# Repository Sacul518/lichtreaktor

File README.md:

# Lichtreaktor

I'm designing a small, round arc-reactor lookalike that produces light in cool patterns. The plan is to press the rotary encoder to switch patterns, and turn it to control the brightness.

The PCB is 90 mm across, with 24 blue LEDs around the edge, a knob in the middle and a XIAO near the top for USB-C access. Six groups of four LEDs will be controlled independently. Tiny reactor, zero fusion involved.

The LEDs look red in KiCad's default 3D model, but the actual parts are blue. The XIAO and rotary encoder don't have 3D models loaded, so their positions look empty here.

## Where it's at

The schematic and PCB layout are done! All 24 LEDs are placed, the traces are routed, and both copper layers have a GND fill. The LEDs, transistors, encoder and XIAO sit on the front; the resistors sit on the back. Getting everything onto a round board took a few attempts, but it fits.

The latest KiCad check (12 October 2026) reports **0 errors, 0 unconnected items and 0 schematic/PCB mismatches**. There are still 24 silkscreen warnings about overlapping print, small text and print near the board edge. Those are accepted for this layout; parts of the print may be clipped during manufacturing. The USB connector intentionally sticks out a little at the top.

This is still a design, not a tested reactor. The [firmware](firmware/README.md) is written, with ten light patterns, encoder controls, adjustable speed, automatic playback, pause, a group test and USB diagnostics. Final part and mechanical checks, supplier prices, fabrication files, soldering and testing on the actual board are next.

## How it works

USB supplies 5 V through the XIAO. Each LED has its own 220 Ω resistor, and each group of four shares a BC337 transistor that switches its connection to GND. The XIAO drives the six transistors through 470 Ω base resistors; 100 kΩ pull-downs keep them off when the control pins aren't being driven. PWM will let the firmware dim each group separately.

The encoder has two rotation signals and a push button, with three 10 kΩ pull-ups to 3.3 V. Turning it will change the brightness, and pressing it will change the pattern. The GND fills keep clearance from the other nets and use thermal reliefs so the pads are easier to hand-solder.

## What will I need to build this?

- Seeed Studio XIAO RP2040 (same one I used for my super cool and sick Hackpad)
- 24 blue LEDs (WP7113QBD/D)
- 24 LED resistors (220 Ω, 1/4 W), one per LED
- A PCB (self-designed ofc)
- 6 BC337 NPN transistors, one per group of four LEDs
- 6 transistor base resistors (470 Ω, 1/4 W)
- 6 transistor pull-down resistors (100 kΩ, 1/4 W)
- Alps Alpine EC11E18244A5 rotary encoder with push button
- 3 encoder pull-up resistors (10 kΩ, 1/4 W)
- 100 nF ceramic capacitor (at least 25 V)
- 2 seven-pin female headers (2.54 mm pitch) for the XIAO
- 2 matching male headers, if the XIAO doesn't already have them
- USB cable for power and programming through the XIAO's USB-C port

[Design BOM with KiCad symbols and footprints](bom.csv). Exact resistor, capacitor and header parts, supplier prices and final mechanical checks are still pending.

## LED placement

The LEDs sit on a 38 mm radius circle, with a gap at the top for the XIAO and USB connector. I kept the [coordinate calculations here](docs/led-placement.md) so this page stays readable.

## Design files

Open [the KiCad project](hardware/Lichtreaktor/Lichtreaktor.kicad_pro) to see the schematic and PCB. The project includes its XIAO symbol and footprint libraries; their source and adaptations are documented [here](hardware/Lichtreaktor/libraries/SOURCES.md).

## A closer look

### PCB layout

### Front and back

### Schematic

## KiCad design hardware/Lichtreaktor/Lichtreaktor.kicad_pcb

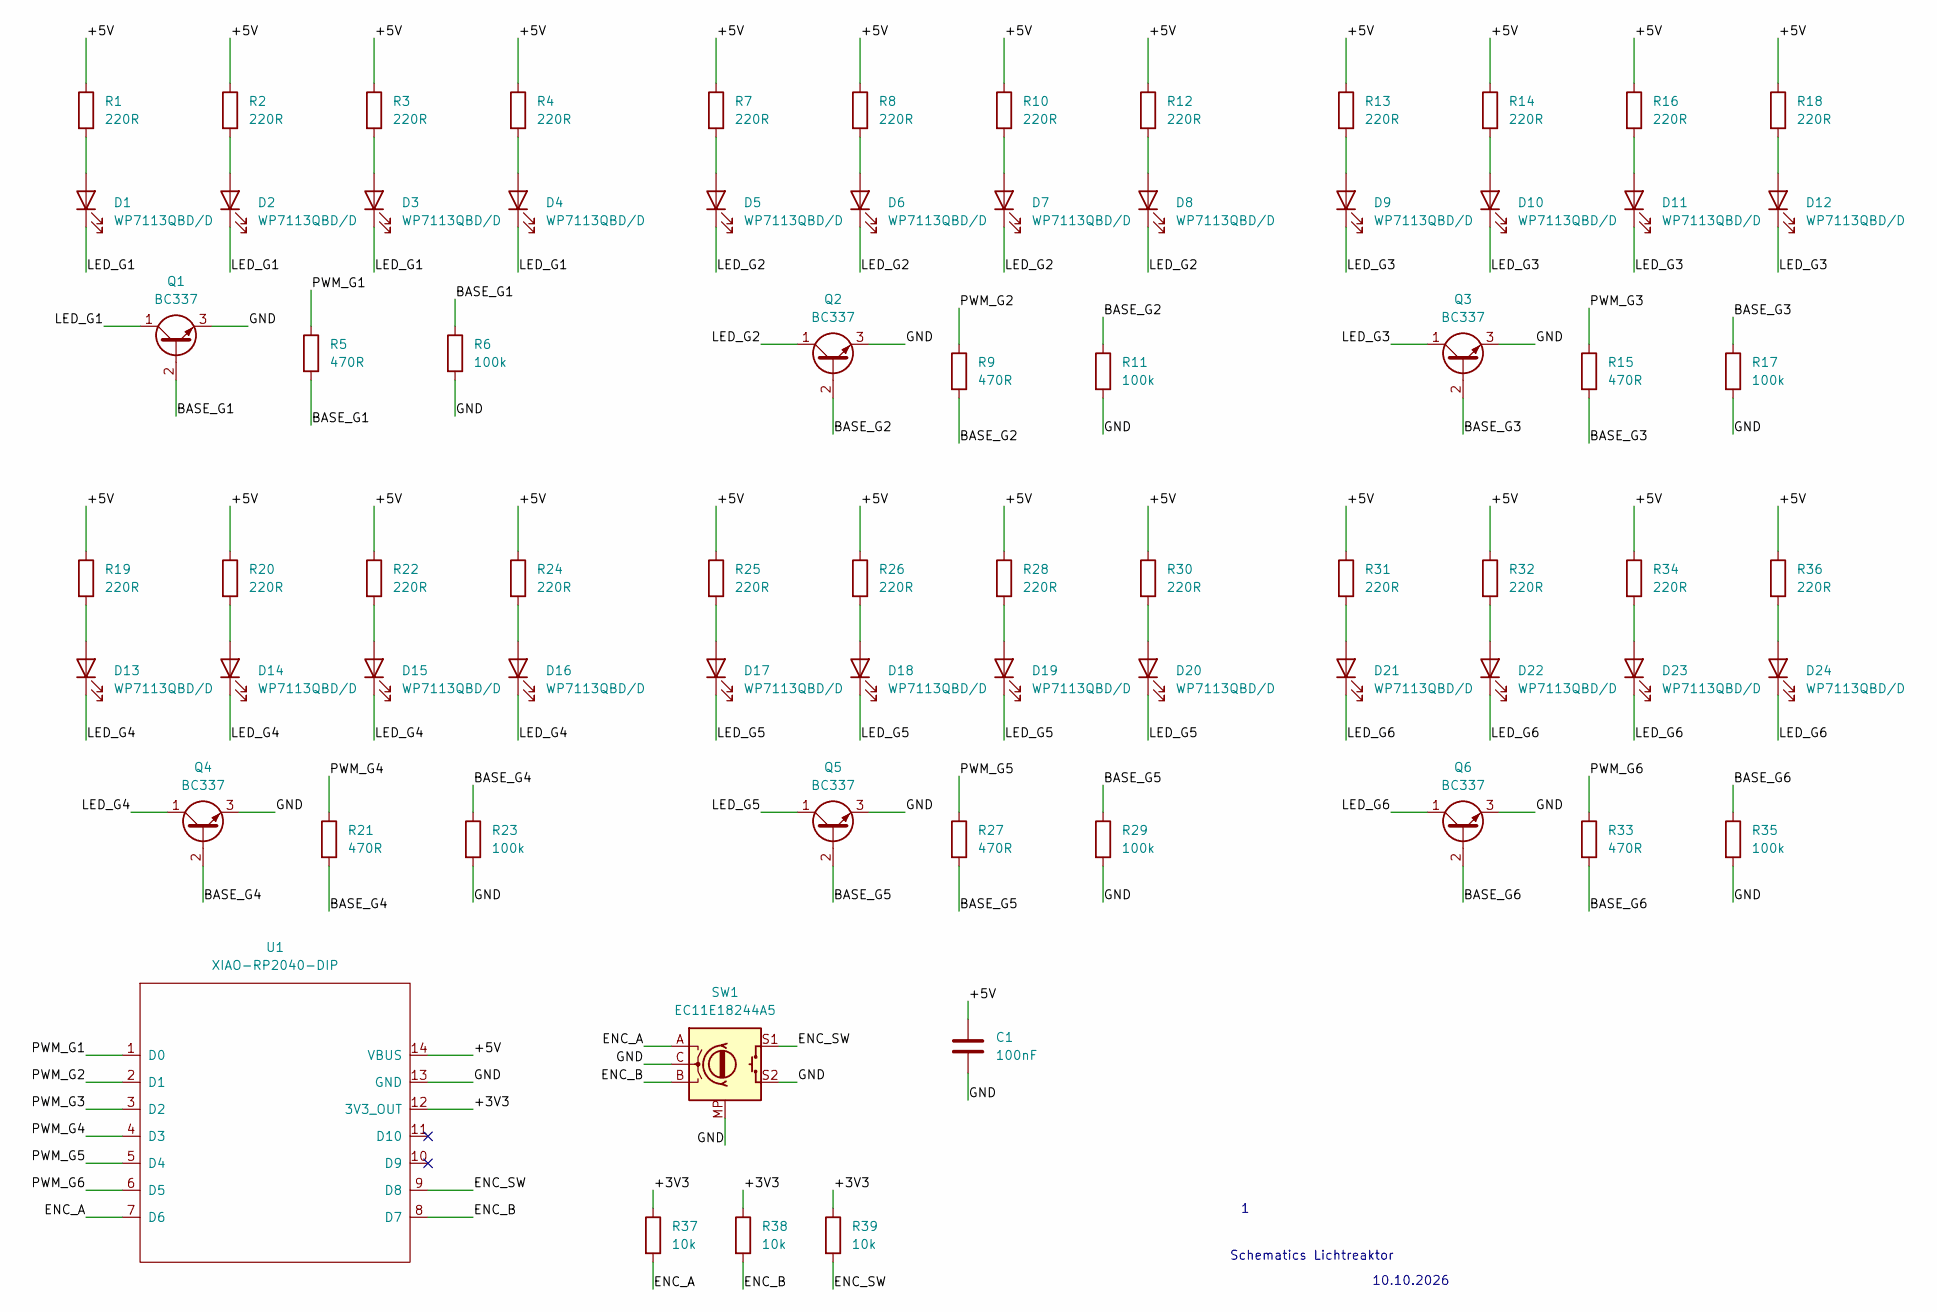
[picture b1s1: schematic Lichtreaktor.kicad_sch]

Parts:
C1: 100nF; C_Disc_D5.0mm_W2.5mm_P5.00mm
D1, D2, D3, D4, D5, D6, D7, D8, D9, D10, D11, D12, D13, D14, D15, D16, D17, D18, D19, D20, D21, D22, D23, D24: WP7113QBD/D; LED_D5.0mm
Q1, Q2, Q3, Q4, Q5, Q6: BC337; TO-92_Inline
R1, R2, R3, R4, R7, R8, R10, R12, R13, R14, R16, R18, R19, R20, R22, R24, R25, R26, R28, R30, R31, R32, R34, R36: 220R; R_Axial_DIN0207_L6.3mm_D2.5mm_P7.62mm_Horizontal
R5, R9, R15, R21, R27, R33: 470R; R_Axial_DIN0207_L6.3mm_D2.5mm_P7.62mm_Horizontal
R6, R11, R17, R23, R29, R35: 100k; R_Axial_DIN0207_L6.3mm_D2.5mm_P7.62mm_Horizontal
R37, R38, R39: 10k; R_Axial_DIN0207_L6.3mm_D2.5mm_P7.62mm_Horizontal
SW1: EC11E18244A5; RotaryEncoder_Alps_EC11E-Switch_Vertical_H20mm
U1: XIAO-RP2040-DIP

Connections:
/+3V3: R37.1, R38.1, R39.1, U1.12 (3V3_OUT)
/+5V: C1.1, R1.1, R2.1, R3.1, R4.1, R7.1, R8.1, R10.1, R12.1, R13.1, R14.1, R16.1, R18.1, R19.1, R20.1, R22.1, R24.1, R25.1, R26.1, R28.1, R30.1, R31.1, R32.1, R34.1, R36.1, U1.14 (VBUS)
/BASE_G1: Q1.2 (B), R5.2, R6.1
/BASE_G2: Q2.2 (B), R9.2, R11.1
/BASE_G3: Q3.2 (B), R15.2, R17.1
/BASE_G4: Q4.2 (B), R21.2, R23.1
/BASE_G5: Q5.2 (B), R27.2, R29.1
/BASE_G6: Q6.2 (B), R33.2, R35.1
/ENC_A: R37.2, SW1.A, U1.7 (D6)
/ENC_B: R38.2, SW1.B, U1.8 (D7)
/ENC_SW: R39.2, SW1.S1, U1.9 (D8)
/GND: C1.2, Q1.3 (E), Q2.3 (E), Q3.3 (E), Q4.3 (E), Q5.3 (E), Q6.3 (E), R6.2, R11.2, R17.2, R23.2, R29.2, R35.2, SW1.C, SW1.MP, SW1.S2, U1.13 (GND)
/LED_G1: D1.1 (K), D2.1 (K), D3.1 (K), D4.1 (K), Q1.1 (C)
/LED_G2: D5.1 (K), D6.1 (K), D7.1 (K), D8.1 (K), Q2.1 (C)
/LED_G3: D9.1 (K), D10.1 (K), D11.1 (K), D12.1 (K), Q3.1 (C)
/LED_G4: D13.1 (K), D14.1 (K), D15.1 (K), D16.1 (K), Q4.1 (C)
/LED_G5: D17.1 (K), D18.1 (K), D19.1 (K), D20.1 (K), Q5.1 (C)
/LED_G6: D21.1 (K), D22.1 (K), D23.1 (K), D24.1 (K), Q6.1 (C)
/PWM_G1: R5.1, U1.1 (D0)
/PWM_G2: R9.1, U1.2 (D1)
/PWM_G3: R15.1, U1.3 (D2)
/PWM_G4: R21.1, U1.4 (D3)
/PWM_G5: R27.1, U1.5 (D4)
/PWM_G6: R33.1, U1.6 (D5)
unnamed: D1.2 (A), R1.2
unnamed: D2.2 (A), R2.2
unnamed: D3.2 (A), R3.2
unnamed: D4.2 (A), R4.2
unnamed: D5.2 (A), R7.2
unnamed: D6.2 (A), R8.2
unnamed: D7.2 (A), R10.2
unnamed: D8.2 (A), R12.2
unnamed: D9.2 (A), R13.2
unnamed: D10.2 (A), R14.2
unnamed: D11.2 (A), R16.2
unnamed: D12.2 (A), R18.2
unnamed: D13.2 (A), R19.2
unnamed: D14.2 (A), R20.2
unnamed: D15.2 (A), R22.2
unnamed: D16.2 (A), R24.2
unnamed: D17.2 (A), R25.2
unnamed: D18.2 (A), R26.2
unnamed: D19.2 (A), R28.2
unnamed: D20.2 (A), R30.2
unnamed: D21.2 (A), R31.2
unnamed: D22.2 (A), R32.2
unnamed: D23.2 (A), R34.2
unnamed: D24.2 (A), R36.2

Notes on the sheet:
10.10.2026
Schematics Lichtreaktor

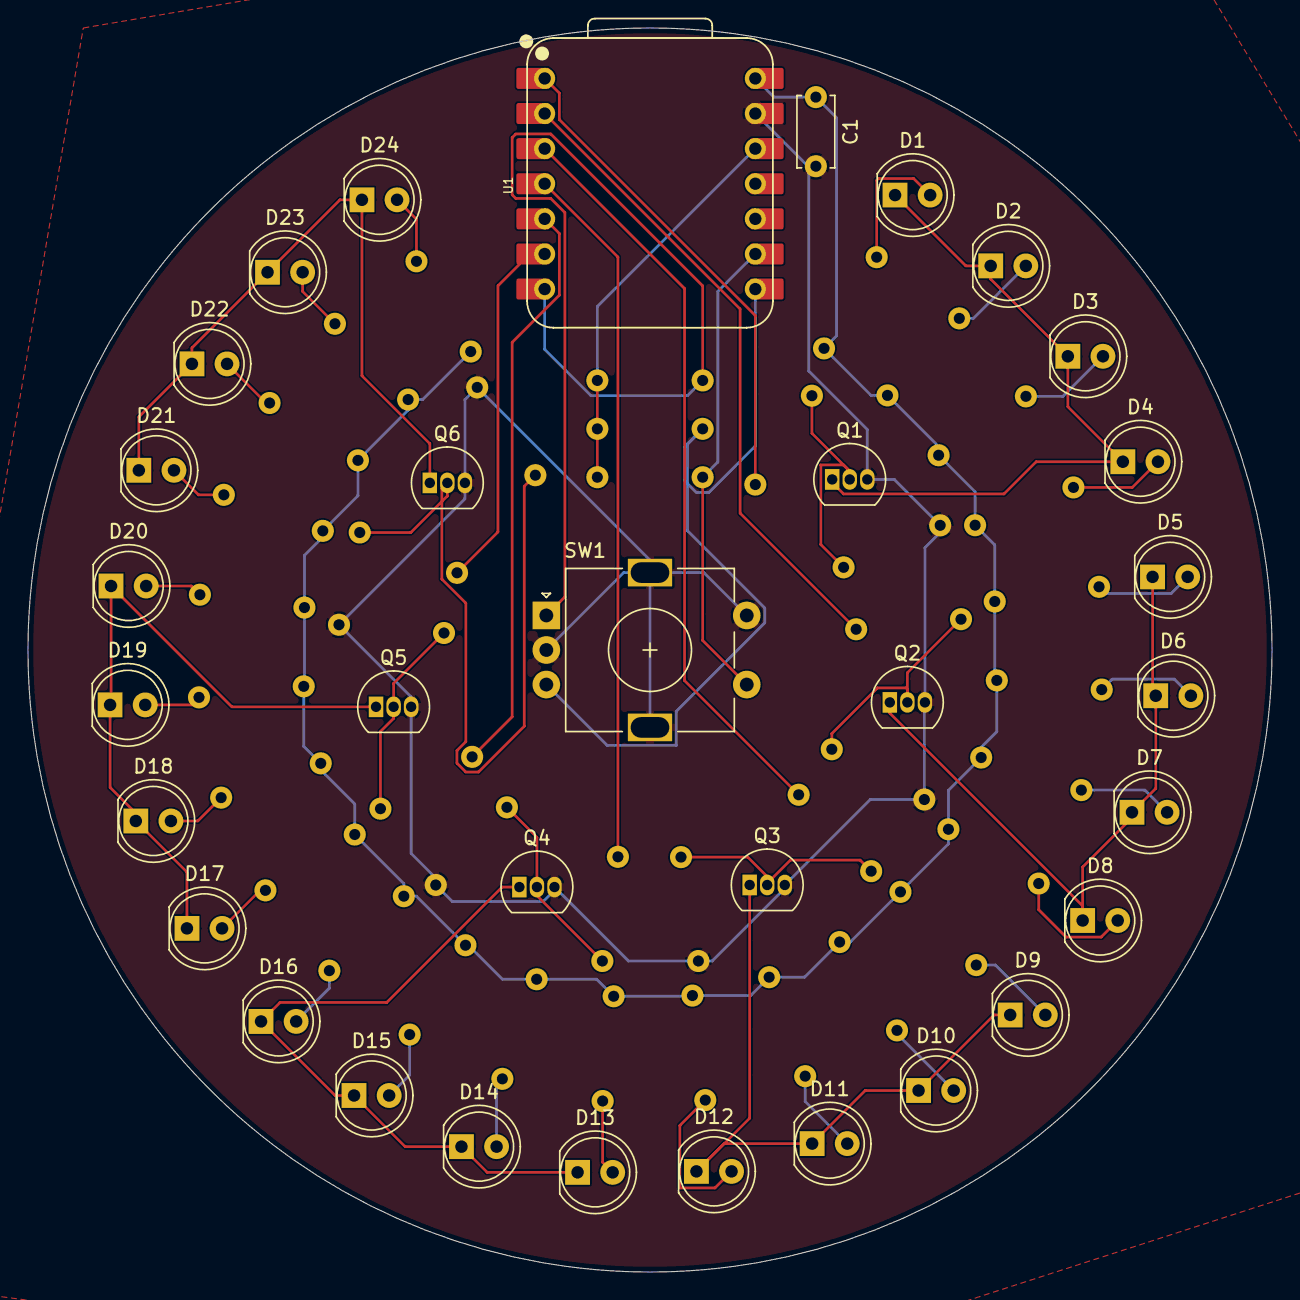
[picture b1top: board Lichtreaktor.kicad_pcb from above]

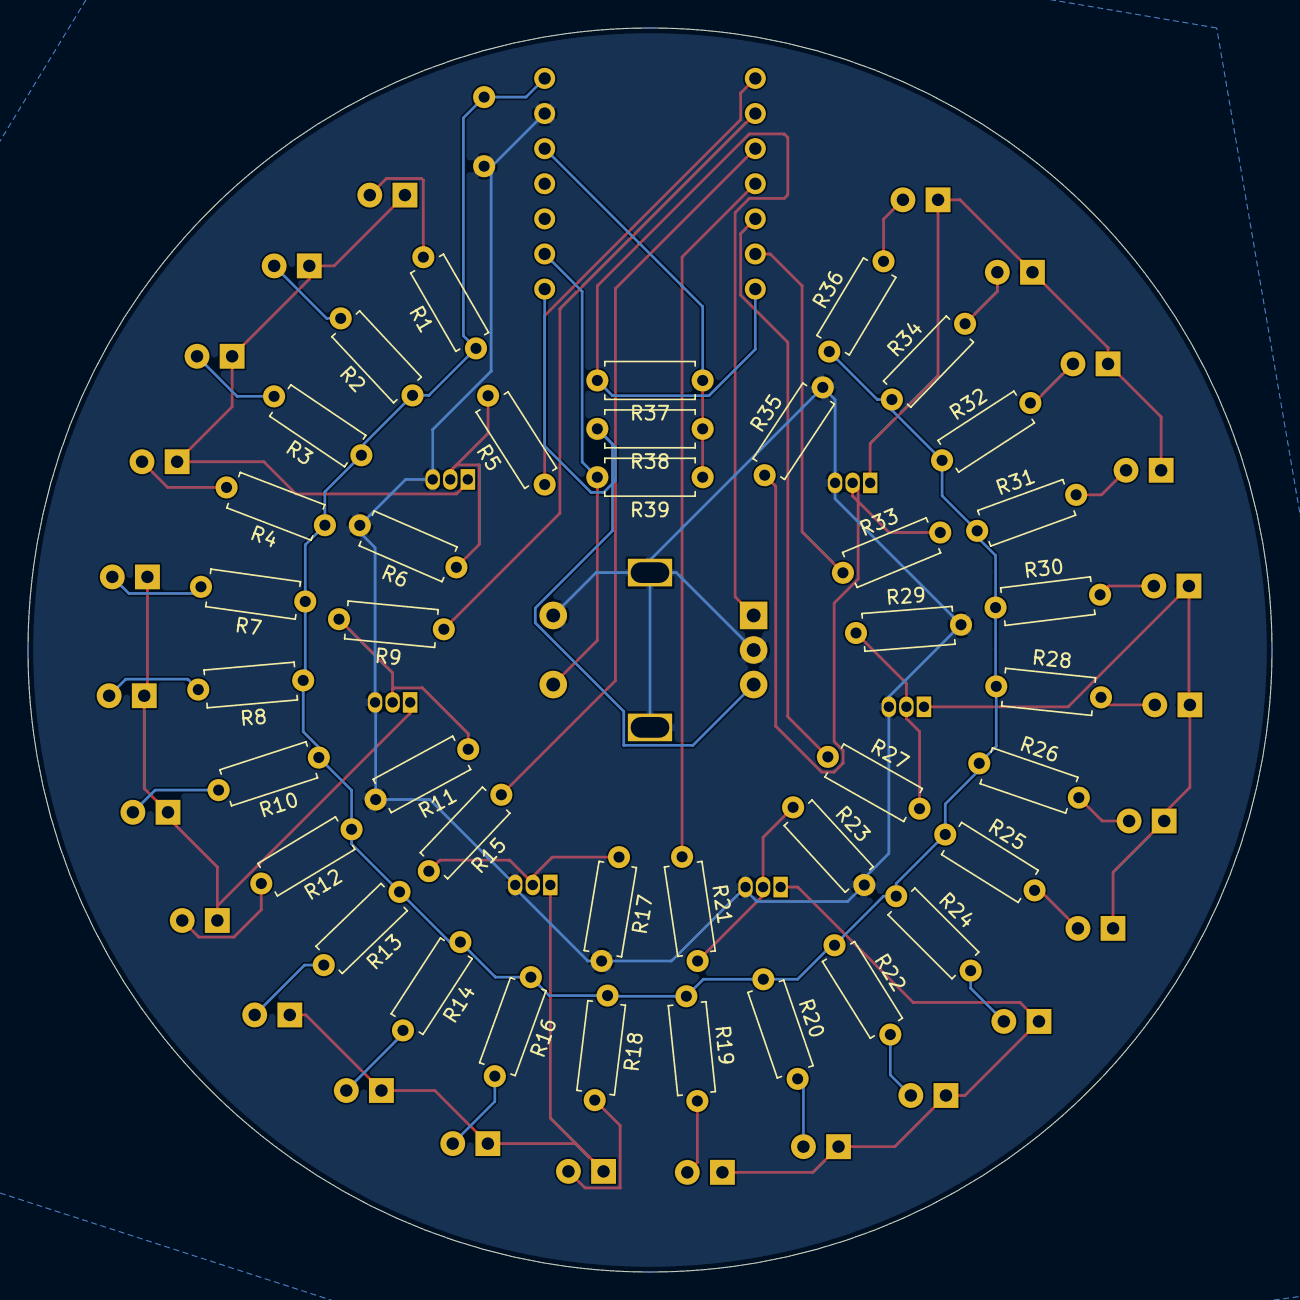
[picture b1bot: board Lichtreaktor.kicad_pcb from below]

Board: 2 copper layers, 90.0 x 90.0 mm, 72 parts (39 on the bottom side), 48 nets.

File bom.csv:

"References","Quantity","Value","Description","KiCad_Symbol","Footprint","Manufacturer","MPN","Datasheet_URL","Notes","Status","Unit_Price_EUR","Supplier_URL"
"U1","1","XIAO RP2040","Controller module with USB-C","Seeed_XIAO:XIAO-RP2040-DIP","Seeed_XIAO:XIAO-RP2040-DIP","Seeed Studio","102010428","https://wiki.seeedstudio.com/XIAO-RP2040/","Project symbol adapted from official Seeed symbol for the 14 side pins. Official DIP footprint with unavailable 3D references removed. See hardware/Lichtreaktor/libraries/SOURCES.md.","Design selection; price pending","",""
"MODULE_SOCKETS","2","Socket 1x07 2.54mm","Female socket for XIAO module","","","","","","Purchased mounting parts; already represented by the module DIP footprint, not additional schematic symbols. Rows 15.24mm apart. Check socket height and USB clearance before ordering.","Mechanical part selection pending","",""
"MODULE_HEADERS","2","Header 1x07 2.54mm","Male header fitted to XIAO module","","","","","","Only needed if module does not already include soldered headers. Not an extra component in the carrier schematic.","Check module contents","",""
"D1, D2, D3, D4, D5, D6, D7, D8, D9, D10, D11, D12, D13, D14, D15, D16, D17, D18, D19, D20, D21, D22, D23, D24","24","WP7113QBD/D","Blue diffuse 5mm LED","Device:LED","LED_THT:LED_D5.0mm","Kingbright","WP7113QBD/D","https://www.kingbrightusa.com/images/catalog/SPEC/WP7113QBD-D.pdf","Six groups of four parallel branches. Each LED has its own 220 ohm series resistor. Symbol pin 1=K (cathode); pin 2=A (anode).","Design selection; price pending","",""
"R1, R2, R3, R4, R7, R8, R10, R12, R13, R14, R16, R18, R19, R20, R22, R24, R25, R26, R28, R30, R31, R32, R34, R36","24","220R","LED current-limiting resistor; 0.25W; 1%","Device:R","Resistor_THT:R_Axial_DIN0207_L6.3mm_D2.5mm_P7.62mm_Horizontal","","","","One resistor per LED. Nominal estimate: (5V - 3.3V - 0.2V) / 220 ohm = 6.8mA. Actual current depends on LED and transistor. Select body approximately 6.3 x 2.5mm.","Exact part and price pending","",""
"Q1, Q2, Q3, Q4, Q5, Q6","6","BC337","NPN transistor switching one LED group to ground","Transistor_BJT:BC337","Package_TO_SOT_THT:TO-92_Inline","onsemi","BC33725BU","https://www.onsemi.com/pdf/datasheet/bc337-fsc-d.pdf","Straight-lead BU package. Pin 1=collector; 2=base; 3=emitter. Use 470 ohm from GPIO to base and 100k from base to emitter. Do not substitute a transistor without checking pinout.","Design selection; price pending","",""
"R5, R9, R15, R21, R27, R33","6","470R","Transistor base resistor; 0.25W; 1%","Device:R","Resistor_THT:R_Axial_DIN0207_L6.3mm_D2.5mm_P7.62mm_Horizontal","","","","Limits GPIO current into transistor base. About (3.3V - 0.8V) / 470 ohm = 5.3mA per enabled group. Confirm GPIO drive configuration in firmware.","Exact part and price pending","",""
"R6, R11, R17, R23, R29, R35","6","100k","Transistor base pull-down resistor; 0.25W; 1%","Device:R","Resistor_THT:R_Axial_DIN0207_L6.3mm_D2.5mm_P7.62mm_Horizontal","","","","One between base and emitter of each transistor. Keeps LEDs off while GPIO is not driven during boot/reset.","Exact part and price pending","",""
"SW1","1","EC11E18244A5","Rotary encoder with momentary push switch","Device:RotaryEncoder_Switch_MP","Rotary_Encoder:RotaryEncoder_Alps_EC11E-Switch_Vertical_H20mm","Alps Alpine","EC11E18244A5","https://tech.alpsalpine.com/e/products/detail/EC11E18244A5/","18 pulses; 36 detents; 20mm flat shaft. Encoder common and one switch contact to GND. A/B and other switch contact to GPIO with 3.3V pull-ups. Software debouncing required. Final dimensions must be compared with selected part drawing before PCB release.","Design selection; mechanical check and price pending","",""
"R37, R38, R39","3","10k","Encoder A/B and push-switch pull-up; 0.25W; 1%","Device:R","Resistor_THT:R_Axial_DIN0207_L6.3mm_D2.5mm_P7.62mm_Horizontal","","","","One from each of encoder A/B and switch GPIO to 3V3. Never pull these GPIO signals up to 5V.","Exact part and price pending","",""
"C1","1","100nF","Ceramic supply decoupling capacitor; >=25V","Device:C","Capacitor_THT:C_Disc_D5.0mm_W2.5mm_P5.00mm","","","","Between +5V and GND near LED supply distribution. Select 5mm lead pitch and body fitting this footprint. XIAO already has onboard regulator decoupling.","Exact part and price pending","",""
"PCB","1","Lichtreaktor carrier","Custom two-layer PCB","","","","","","Round two-layer PCB; 90mm diameter (45mm radius). LED centre ring radius 38mm. Routing and ground pours completed; final mechanical checks and fabrication quote pending. USB power through XIAO only; no battery or separate power input.","Routed layout; fabrication quote pending","",""
